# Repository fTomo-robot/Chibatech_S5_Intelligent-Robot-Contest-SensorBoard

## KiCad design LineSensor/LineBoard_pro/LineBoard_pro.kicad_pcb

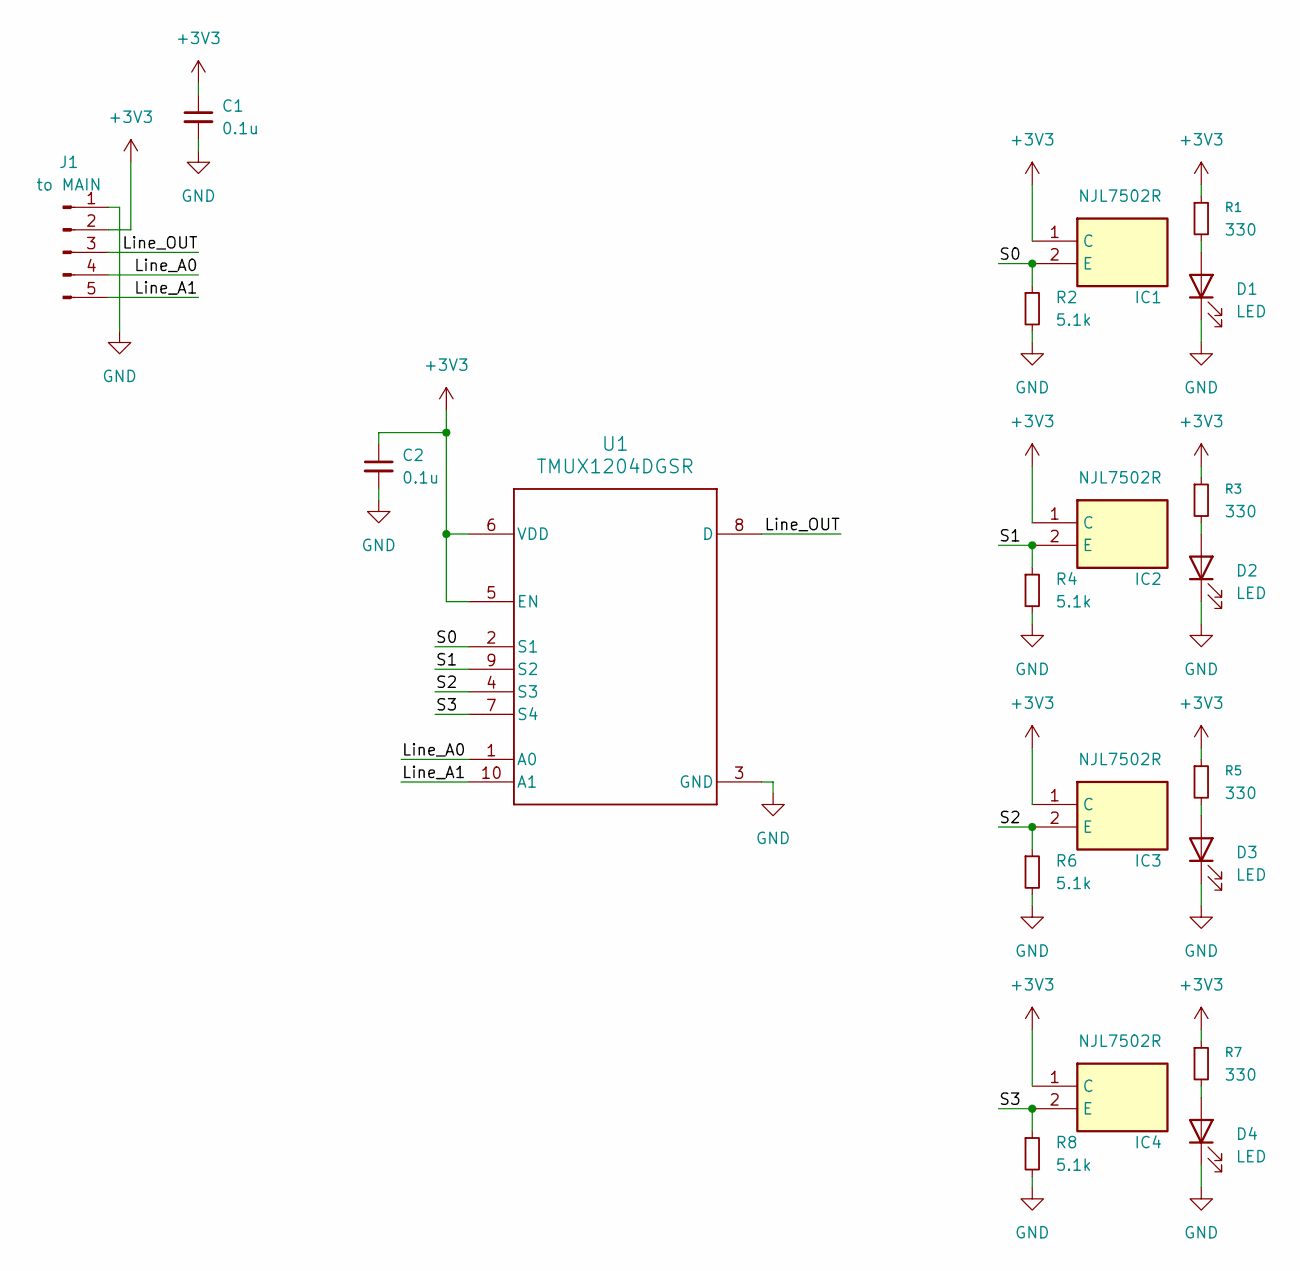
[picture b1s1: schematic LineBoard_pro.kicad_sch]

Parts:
C1, C2: 0.1u; C_0603_1608Metric
D1, D2, D3, D4: LED; LED_0603_1608Metric
IC1, IC2, IC3, IC4: NJL7502R; Manufacturer_Part_Number NJL7502R
J1: to MAIN; JST_PH_B5B-PH-K_1x05_P2.00mm_Vertical
R1, R3, R5, R7: 330; R_0603_1608Metric
R2, R4, R6, R8: 5.1k; R_0603_1608Metric
U1: TMUX1204DGSR; DGS0010A-IPC_A

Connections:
+3V3: C1.1, C2.1, IC1.1 (C), IC2.1 (C), IC3.1 (C), IC4.1 (C), J1.2, R1.1, R3.1, R5.1, R7.1, U1.5 (EN), U1.6 (VDD)
/Line_A0: J1.4, U1.1 (A0)
/Line_A1: J1.5, U1.10 (A1)
/Line_OUT: J1.3, U1.8 (D)
/S0: IC1.2 (E), R2.1, U1.2 (S1)
/S1: IC2.2 (E), R4.1, U1.9 (S2)
/S2: IC3.2 (E), R6.1, U1.4 (S3)
/S3: IC4.2 (E), R8.1, U1.7 (S4)
GND: C1.2, C2.2, D1.1 (K), D2.1 (K), D3.1 (K), D4.1 (K), J1.1, R2.2, R4.2, R6.2, R8.2, U1.3 (GND)
unnamed: D1.2 (A), R1.2
unnamed: D2.2 (A), R3.2
unnamed: D3.2 (A), R5.2
unnamed: D4.2 (A), R7.2

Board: 2 copper layers, 20 parts (0 on the bottom side), 13 nets, no tracks yet.

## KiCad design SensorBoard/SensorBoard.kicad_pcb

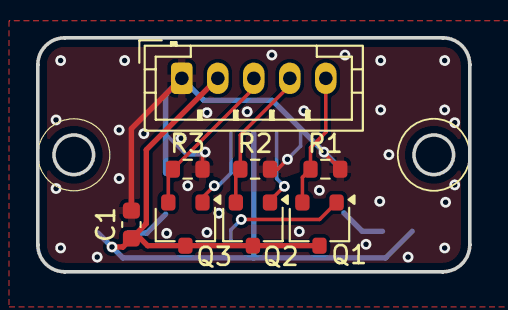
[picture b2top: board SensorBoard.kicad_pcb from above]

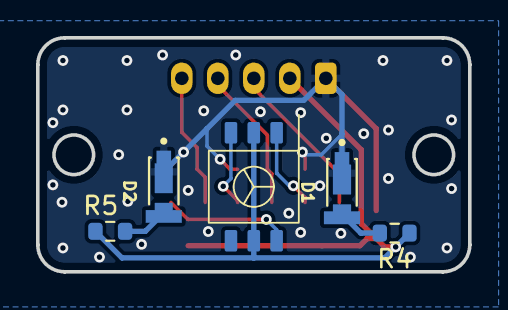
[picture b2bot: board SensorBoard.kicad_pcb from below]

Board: 2 copper layers, 24.0 x 13.0 mm, 13 parts (5 on the bottom side), 10 nets.

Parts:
C1: 0.1u; C_0603_1608Metric
D1, D2: MP-3014-1100-50-70; LED_MP-3014-1100-50-70
J1: to MAIN; JST_PH_B5B-PH-K_1x05_P2.00mm_Vertical
Q1, Q2, Q3: 2SC2712-Y; SC-59
R1, R2, R3: 5.1k; R_0603_1608Metric
R4, R5: 10; R_0603_1608Metric
S1: S9032-02

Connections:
+3V3: C1.1, J1.2, Q1.3 (C), Q2.3 (C), Q3.3 (C), R4.1, R5.1, S1.2 (Cathode), S1.5 (Cathode)
/Blue: Q1.1 (B), S1.6 (Anode_BLUE)
/Green: Q2.1 (B), S1.3 (Anode_Green)
/Red: Q3.1 (B), S1.1 (Anode_Red)
/S_B: J1.5, Q1.2 (E), R1.1
/S_G: J1.4, Q2.2 (E), R2.1
/S_R: J1.3, Q3.2 (E), R3.1
GND: C1.2, D1.C, D2.C, J1.1, R1.2, R2.2, R3.2
unnamed: D1.A, R4.2
unnamed: D2.A, R5.2

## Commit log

2026-04-22 配線開始
2026-04-22 配線終わり
2026-04-22 フットプリント割り当て終了
2026-04-22 部品配置はじめ
2026-04-22 仮配線終了
2026-04-22 パターン終了
2026-04-23 部品仮配置
2026-04-24 部品配置してみた
2026-04-27 部品移動
